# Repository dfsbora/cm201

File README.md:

<h1 align="center">CM-201 Projeto e Fabricação de Robôs Móveis</h1>
<p align="center">Laboratórios</p>

## Requisitos
KiCad 5.1.1 

Grupo 02.

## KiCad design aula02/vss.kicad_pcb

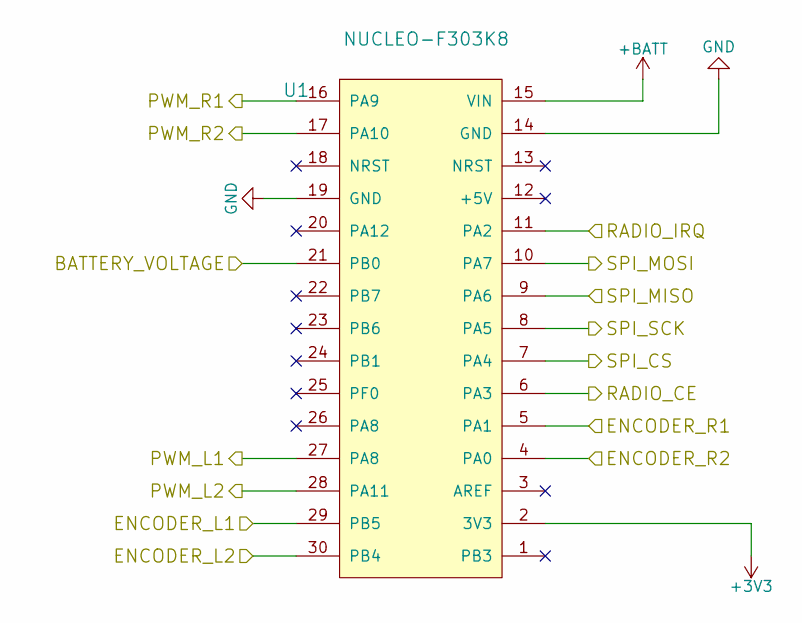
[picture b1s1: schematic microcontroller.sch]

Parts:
U1: NUCLEO-F303K8; NUCLEO-F3

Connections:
+BATT: U1.15 (VIN); also elsewhere on the board
/Microcontroller/BATTERY_VOLTAGE: U1.21 (PB0); also elsewhere on the board
/MotorL/ENCODER_1: U1.29 (PB5); also elsewhere on the board
/MotorL/ENCODER_2: U1.30 (PB4); also elsewhere on the board
/MotorL/PWM_1: U1.27 (PA8); also elsewhere on the board
/MotorL/PWM_2: U1.28 (PA11); also elsewhere on the board
/MotorR/ENCODER_1: U1.5 (PA1); also elsewhere on the board
/MotorR/ENCODER_2: U1.4 (PA0); also elsewhere on the board
/MotorR/PWM_1: U1.16 (PA9); also elsewhere on the board
/MotorR/PWM_2: U1.17 (PA10); also elsewhere on the board
/Radio/CE: U1.6 (PA3); also elsewhere on the board
/Radio/CSN: U1.7 (PA4); also elsewhere on the board
/Radio/IRQ: U1.11 (PA2); also elsewhere on the board
/Radio/MISO: U1.9 (PA6); also elsewhere on the board
/Radio/MOSI: U1.10 (PA7); also elsewhere on the board
/Radio/SCK: U1.8 (PA5); also elsewhere on the board
GND: U1.14 (GND), U1.19 (GND); also elsewhere on the board

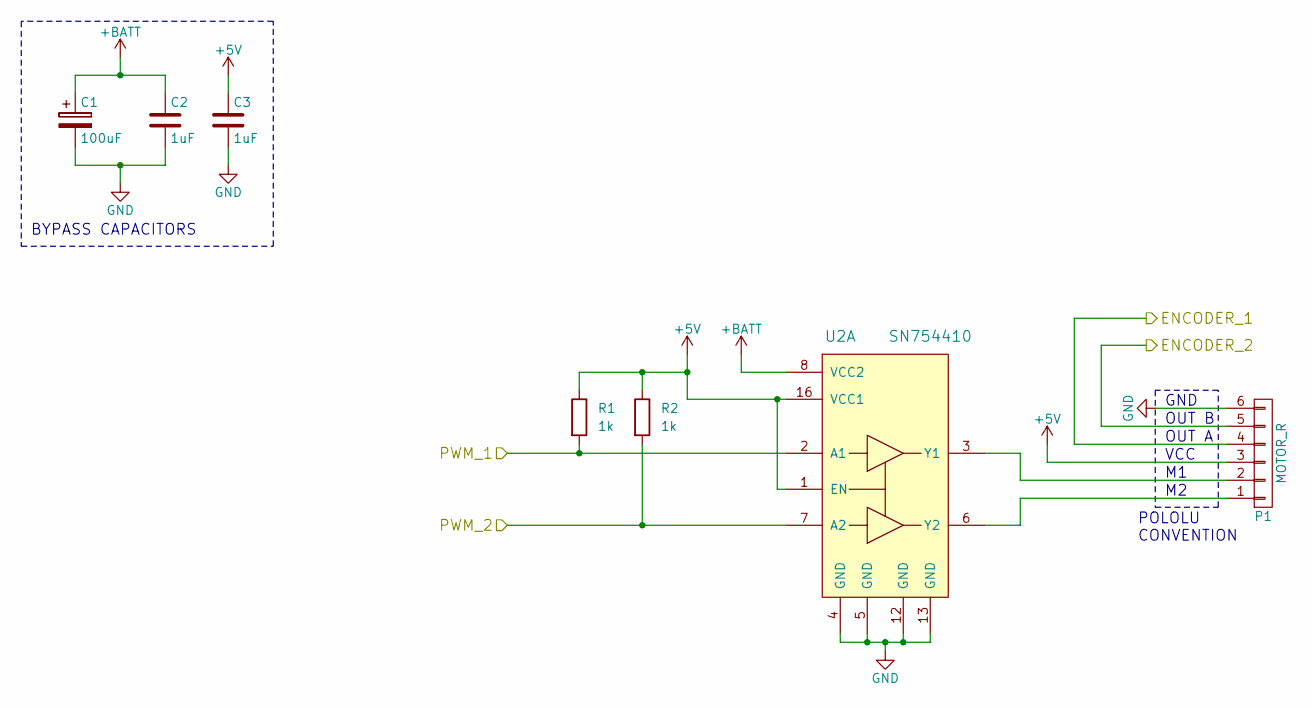
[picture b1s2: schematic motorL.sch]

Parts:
C1: 100uF; CP_Radial_D6.3mm_P2.50mm
C2, C3: 1uF; C_0805_2012Metric_Pad1.15x1.40mm_HandSolder
P1: MOTOR_R; PinHeader_1x06_P2.54mm_Horizontal
R1, R2: 1k; R_1206_3216Metric_Pad1.42x1.75mm_HandSolder
U2: SN754410; DIP-16_W7.62mm_Socket_LongPads

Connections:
+5V: C3.1, P1.3, R1.1, R2.1, U2.1 (EN), U2.16 (VCC1); also elsewhere on the board
+BATT: C1.1, C2.1, U2.8 (VCC2); also elsewhere on the board
/MotorL/ENCODER_1: P1.4; also elsewhere on the board
/MotorL/ENCODER_2: P1.5; also elsewhere on the board
/MotorL/PWM_1: R1.2, U2.2 (A1); also elsewhere on the board
/MotorL/PWM_2: R2.2, U2.7 (A2); also elsewhere on the board
GND: C1.2, C2.2, C3.2, P1.6, U2.4 (GND), U2.5 (GND), U2.12 (GND), U2.13 (GND); also elsewhere on the board
unnamed: P1.1, U2.6 (Y2)
unnamed: P1.2, U2.3 (Y1)

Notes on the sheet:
BYPASS CAPACITORS
VCC
OUT A
OUT B
GND
POLOLU CONVENTION

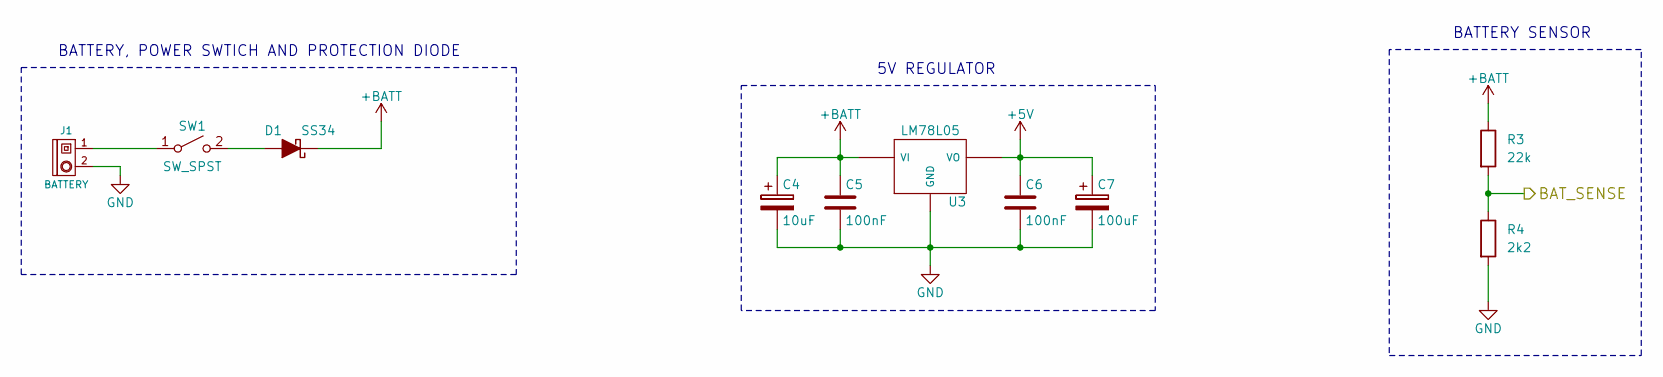
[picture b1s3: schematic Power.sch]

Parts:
C4: 10uF; CP_Radial_D4.0mm_P2.00mm
C5, C6: 100nF; C_1206_3216Metric_Pad1.42x1.75mm_HandSolder
C7: 100uF; CP_Radial_D6.3mm_P2.50mm
D1: SS34; D_SMB_Handsoldering
J1: BATTERY; PinHeader_1x02_P2.54mm_Horizontal
R3: 22k; R_1206_3216Metric_Pad1.42x1.75mm_HandSolder
R4: 2k2; R_1206_3216Metric_Pad1.42x1.75mm_HandSolder
SW1: SW_SPST; PRK22J5DBBNN
U3: LM78L05; SOT-89-3_Handsoldering

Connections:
+5V: C6.1, C7.1, U3.1 (VO); also elsewhere on the board
+BATT: C4.1, C5.1, D1.1 (K), R3.1, U3.3 (VI); also elsewhere on the board
/Microcontroller/BATTERY_VOLTAGE: R3.2, R4.1; also elsewhere on the board
GND: C4.2, C5.2, C6.2, C7.2, J1.2, R4.2, U3.2 (GND); also elsewhere on the board
unnamed: D1.2 (A), SW1.2 (B)
unnamed: J1.1, SW1.1 (A)

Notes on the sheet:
BATTERY SENSOR
BATTERY, POWER SWTICH AND PROTECTION DIODE
5V REGULATOR

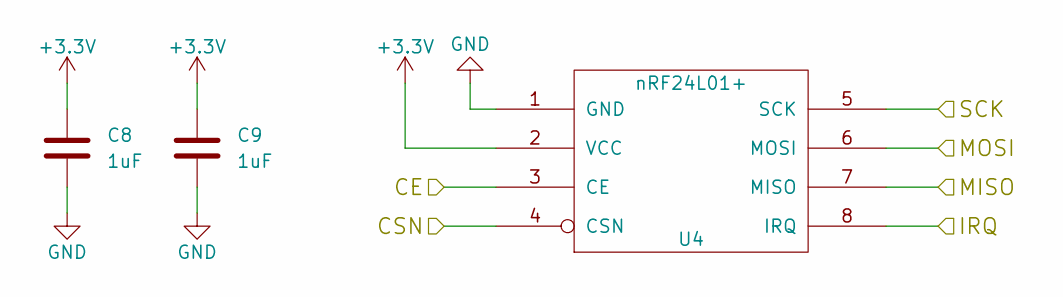
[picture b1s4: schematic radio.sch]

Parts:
C8, C9: 1uF; C_0805_2012Metric_Pad1.15x1.40mm_HandSolder
U4: nRF24L01+; NRF24L01

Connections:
/Radio/CE: U4.3 (CE); also elsewhere on the board
/Radio/CSN: U4.4 (CSN); also elsewhere on the board
/Radio/IRQ: U4.8 (IRQ); also elsewhere on the board
/Radio/MISO: U4.7 (MISO); also elsewhere on the board
/Radio/MOSI: U4.6 (MOSI); also elsewhere on the board
/Radio/SCK: U4.5 (SCK); also elsewhere on the board
GND: C8.2, C9.2, U4.1 (GND); also elsewhere on the board

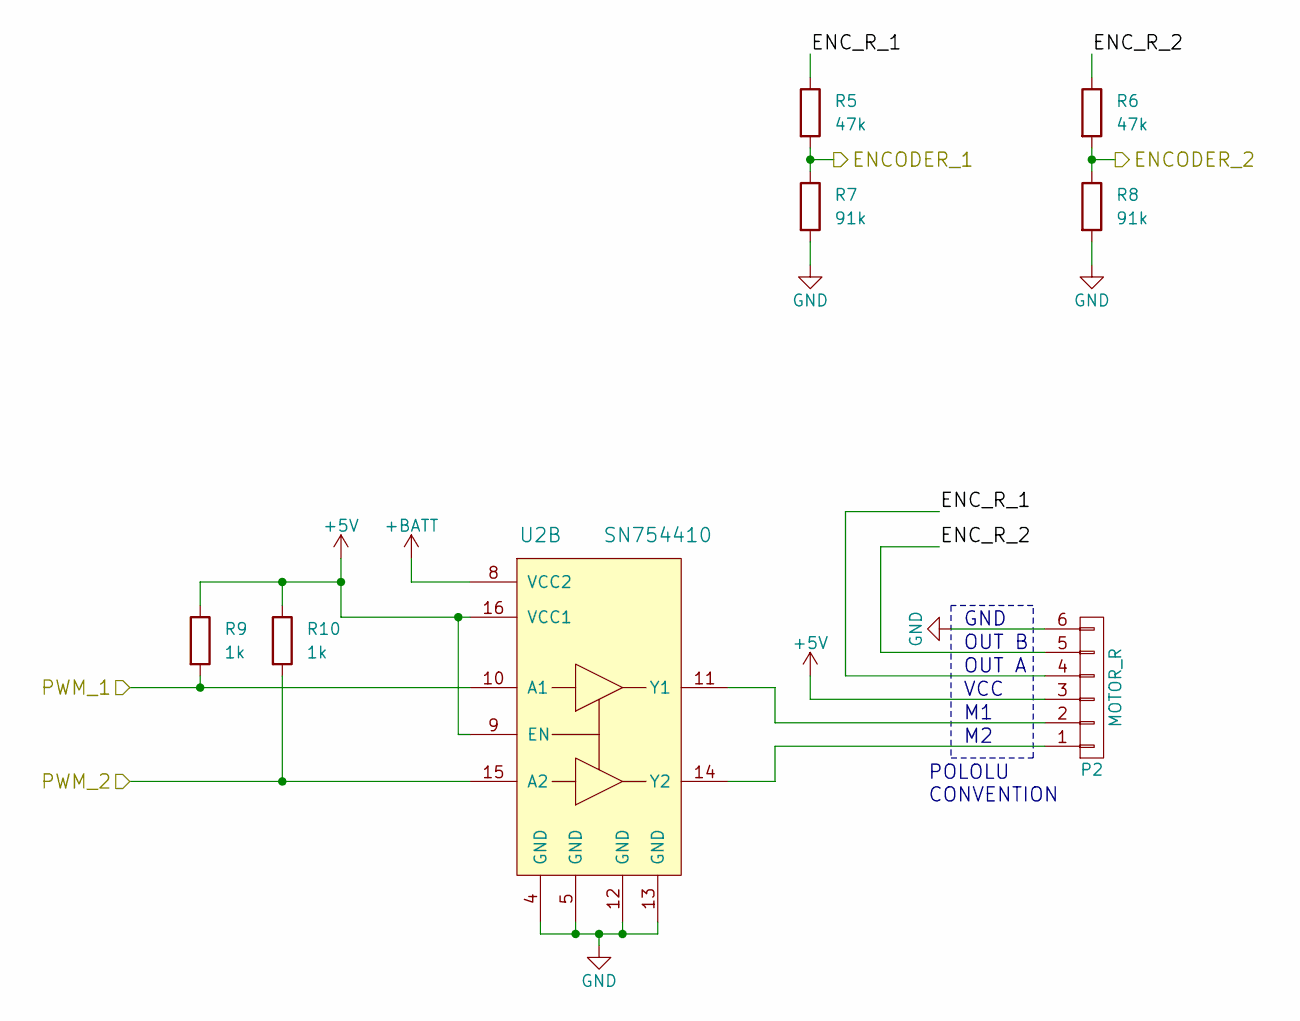
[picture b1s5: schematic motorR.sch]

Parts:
P2: MOTOR_R; PinHeader_1x06_P2.54mm_Horizontal
R5, R6: 47k; R_1206_3216Metric_Pad1.42x1.75mm_HandSolder
R7, R8: 91k; R_1206_3216Metric_Pad1.42x1.75mm_HandSolder
R9, R10: 1k; R_1206_3216Metric_Pad1.42x1.75mm_HandSolder
U2: SN754410; DIP-16_W7.62mm_Socket_LongPads

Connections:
+5V: P2.3, R9.1, R10.1, U2.9 (EN), U2.16 (VCC1); also elsewhere on the board
+BATT: U2.8 (VCC2); also elsewhere on the board
/MotorR/ENCODER_1: R5.2, R7.1; also elsewhere on the board
/MotorR/ENCODER_2: R6.2, R8.1; also elsewhere on the board
/MotorR/ENC_R_1: P2.4, R5.1
/MotorR/ENC_R_2: P2.5, R6.1
/MotorR/PWM_1: R9.2, U2.10 (A1); also elsewhere on the board
/MotorR/PWM_2: R10.2, U2.15 (A2); also elsewhere on the board
GND: P2.6, R7.2, R8.2, U2.4 (GND), U2.5 (GND), U2.12 (GND), U2.13 (GND); also elsewhere on the board
unnamed: P2.1, U2.14 (Y2)
unnamed: P2.2, U2.11 (Y1)

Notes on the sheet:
VCC
OUT A
OUT B
GND
POLOLU CONVENTION

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
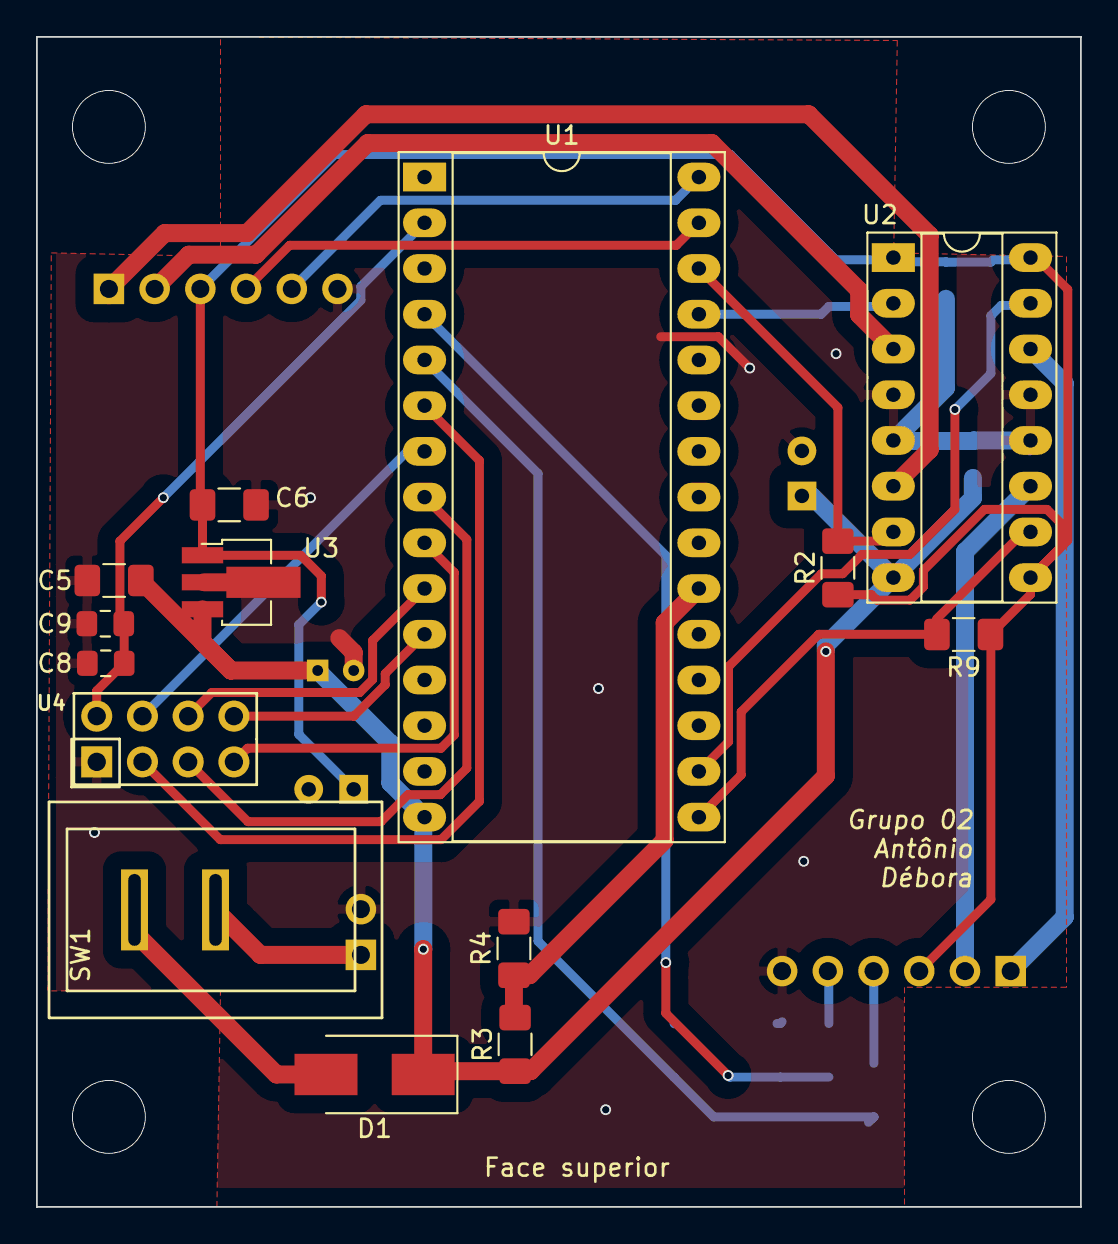
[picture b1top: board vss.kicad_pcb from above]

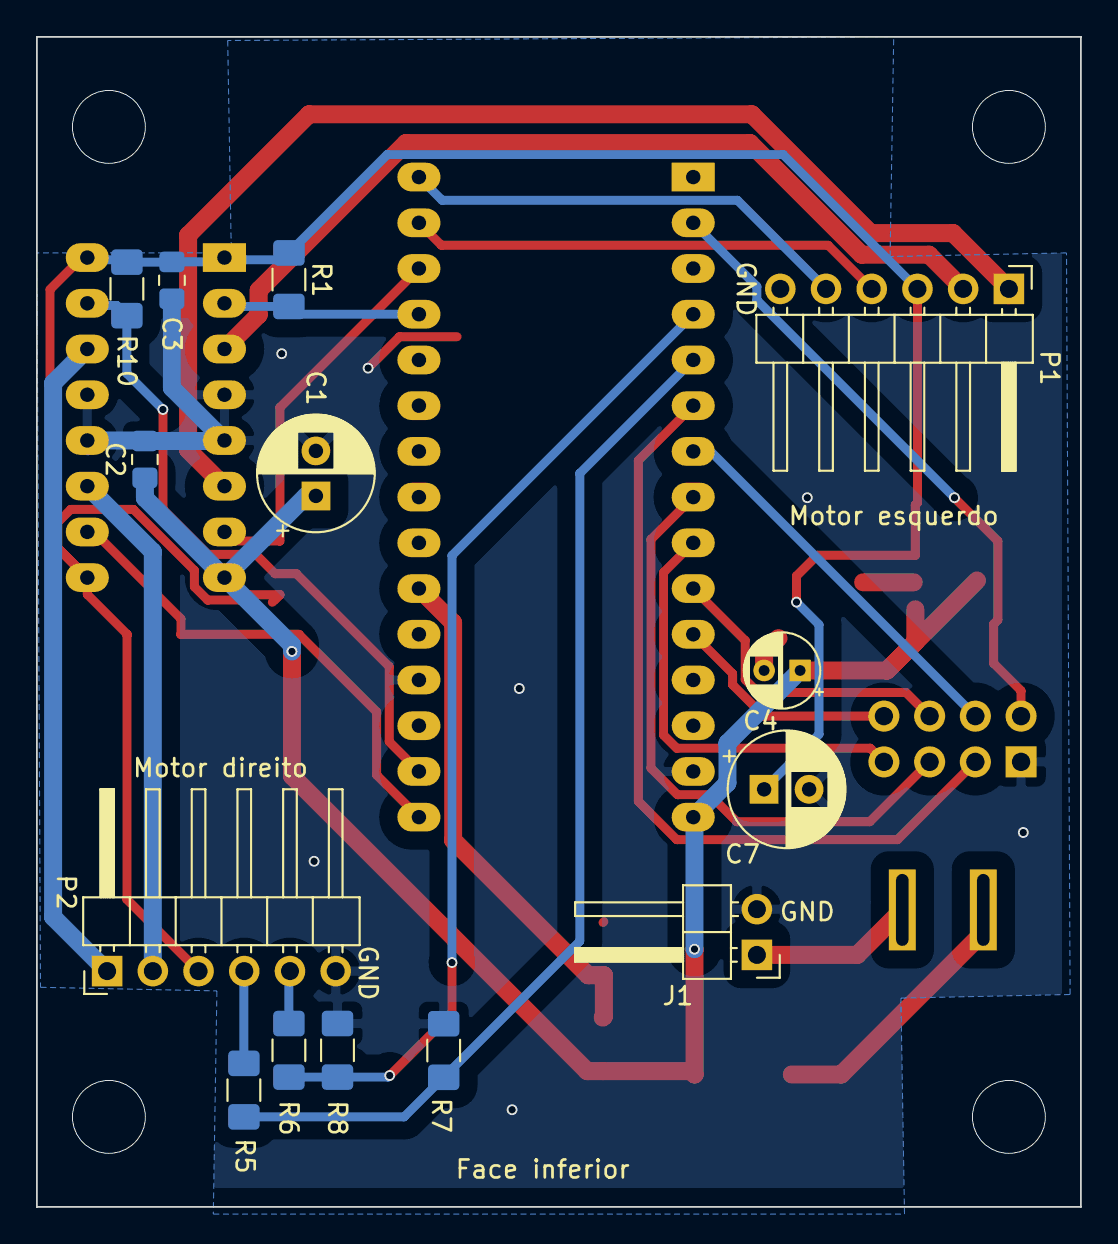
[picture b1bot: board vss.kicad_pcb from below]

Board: 2 copper layers, 58.0 x 65.0 mm, 28 parts (14 on the bottom side), 27 nets.

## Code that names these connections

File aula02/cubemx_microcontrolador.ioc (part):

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Mcu.Name=STM32F303K(6-8)Tx
Mcu.Package=LQFP32
Mcu.UserName=STM32F303K8Tx
PA0.GPIOParameters=GPIO_Label
PA0.GPIO_Label=ENCODER_R1
PA0.Signal=S_TIM2_CH1_ETR
PA1.GPIOParameters=GPIO_Label
PA1.GPIO_Label=ENCODER_R2
PA1.Signal=S_TIM2_CH2
PA10.GPIOParameters=GPIO_Label
PA10.GPIO_Label=PWM_R2
PA10.Signal=S_TIM1_CH3
PA11.GPIOParameters=GPIO_Label
PA11.GPIO_Label=PWM_L2
PA11.Signal=S_TIM1_CH4
PA2.GPIOParameters=GPIO_Label
PA2.GPIO_Label=RADIO_IRQ
PA2.Signal=GPXTI2
PA3.GPIOParameters=GPIO_Label
PA3.GPIO_Label=RADIO_CE
PA3.Signal=GPIO_Output
PA4.GPIOParameters=GPIO_Label
PA4.GPIO_Label=SPI_CS
PA4.Signal=GPIO_Output
PA5.GPIOParameters=GPIO_Label
PA5.GPIO_Label=SPI_SCK
PA5.Mode=Full_Duplex_Master
PA5.Signal=SPI1_SCK
PA6.GPIOParameters=GPIO_Label
PA6.GPIO_Label=SPI_MISO
PA6.Mode=Full_Duplex_Master
PA6.Signal=SPI1_MISO
PA7.GPIOParameters=GPIO_Label
PA7.GPIO_Label=SPI_MOSI
PA7.Mode=Full_Duplex_Master
PA7.Signal=SPI1_MOSI
PA8.GPIOParameters=GPIO_Label
PA8.GPIO_Label=PWM_L1
PA8.Signal=S_TIM1_CH1
PA9.GPIOParameters=GPIO_Label
PA9.GPIO_Label=PWM_R1
PA9.Signal=S_TIM1_CH2
PB0.Signal=ADC1_IN11
PB4.GPIOParameters=GPIO_Label
PB4.GPIO_Label=ENCODER_L2
PB4.Signal=S_TIM3_CH1
PB5.GPIOParameters=GPIO_Label
PB5.GPIO_Label=ENCODER_L1
PB5.Signal=S_TIM3_CH2
RCC.HSEPLLFreq_Value=8000000
RCC.HSE_VALUE=8000000
RCC.SYSCLKFreq_VALUE=8000000

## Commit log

2021-08-14 docs: update README
2021-08-14 add: pcb design v1
2021-08-14 feat: pcb roteamento
2021-08-14 fix: roteamento motor
2021-08-17 add: CAT files
2021-08-20 fix: plano de ground
2021-08-20 fix: vias
2021-08-20 fix: posicao capacitor e planos de ground
2021-08-25 fix: R9 location
2021-08-25 fix: components under radio and filled zones
